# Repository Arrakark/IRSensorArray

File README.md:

# IR Sensor Array

An infra-red sensor array for detecting lines and small objects up to 15cm away.

## PCB Description

### Specs

* 3.3V - 6V input voltage
* Can be used with I2C fast mode using ~2k pullups (try 10k first)
* Can detect lines with high precision and speed
* Can detect objects and surfaces up to 15cm away
* Uses 4-pin JST-XH headers for power and data
* Power and data be daisychained

This project was created using KiCad 5 RC2. Use it to open and edit this design.

### BOM

|      |                                      |                                                               |            |                         |                    |  |  | 
|------|--------------------------------------|---------------------------------------------------------------|------------|-------------------------|--------------------|--|--| 
| "Id" | "Designator"                         | "Package"                                                     | "Quantity" | "Designation"           | "Supplier and ref" |  |  | 
| 1    | "MH2,MH1"                            | "MountingHole_3.2mm_M3"                                       | 2          | "MountingHole_3.2mm_M3" |                    |  |  | 
| 2    | "C1"                                 | "C_Disc_D5.1mm_W3.2mm_P5.00mm"                                | 1          | "0.1uF"                 |                    |  |  | 
| 3    | "C2"                                 | "CP_Radial_D5.0mm_P2.00mm"                                    | 1          | "10uF"                  |                    |  |  | 
| 4    | "C4"                                 | "C_Disc_D5.1mm_W3.2mm_P5.00mm"                                | 1          | "100nF"                 |                    |  |  | 
| 5    | "D1,D2,D3,D4,D5,D6,D7,D8"            | "LED_D5.0mm"                                                  | 8          | "EMITTER"               |                    |  |  | 
| 6    | "J1"                                 | "Measurement_Point_Round-TH_Small"                            | 1          | "EXT_REF"               |                    |  |  | 
| 7    | "Q1,Q2,Q3,Q5,Q6,Q7,Q8,Q4"            | "LED_D5.0mm"                                                  | 8          | "QSD124"                |                    |  |  | 
| 8    | "R1,R2,R4,R6,R8,R10,R12,R14,R16,R18" | "R_Axial_DIN0207_L6.3mm_D2.5mm_P2.54mm_Vertical"              | 10         | "10k0"                  |                    |  |  | 
| 9    | "R3,R5,R7,R9,R11,R13,R15,R17"        | "R_Axial_DIN0207_L6.3mm_D2.5mm_P2.54mm_Vertical"              | 8          | "330R"                  |                    |  |  | 
| 10   | "U1"                                 | "TSSOP-16_4.4x5mm_Pitch0.65mm"                                | 1          | "ADS7828"               |                    |  |  | 
| 11   | "J2"                                 | "JST_XH_B04B-XH-A_04x2.50mm_Straight"                         | 1          | "INPUT"                 |                    |  |  | 
| 12   | "J3"                                 | "JST_XH_B04B-XH-A_04x2.50mm_Straight"                         | 1          | "PASSTHRU"              |                    |  |  | 
| 13   | "JP1"                                | "SolderJumper-3_P1.3mm_Open_RoundedPad1.0x1.5mm_NumberLabels" | 1          | "SB_0"                  |                    |  |  | 
| 14   | "JP2"                                | "SolderJumper-3_P1.3mm_Open_RoundedPad1.0x1.5mm_NumberLabels" | 1          | "REF_5V"                |                    |  |  | 
| 15   | "JP3"                                | "SolderJumper-3_P1.3mm_Open_RoundedPad1.0x1.5mm_NumberLabels" | 1          | "SB_1"                  |                    |  |  | 
| 16   | "G***"                               | "rover"                                                       | 1          | "LOGO"                  |                    |  |  | 

## Installing

Install the sensor array using two M3 screws and standoffs.

## Signal Control

Use the library included with this repo to read the values of the sensors. 

Use the following code to create a sensor array object:
```
SensorArray array1(lookup_table, I2C ID);
```
See the header file for an example.

## License

This project is licensed under the MIT License - see the [LICENSE.md](https://github.com/Arrakark/IRSensorArray/blob/master/LICENSE) file for details

## Acknowledgments

* Special thanks to the V2FC robot team!

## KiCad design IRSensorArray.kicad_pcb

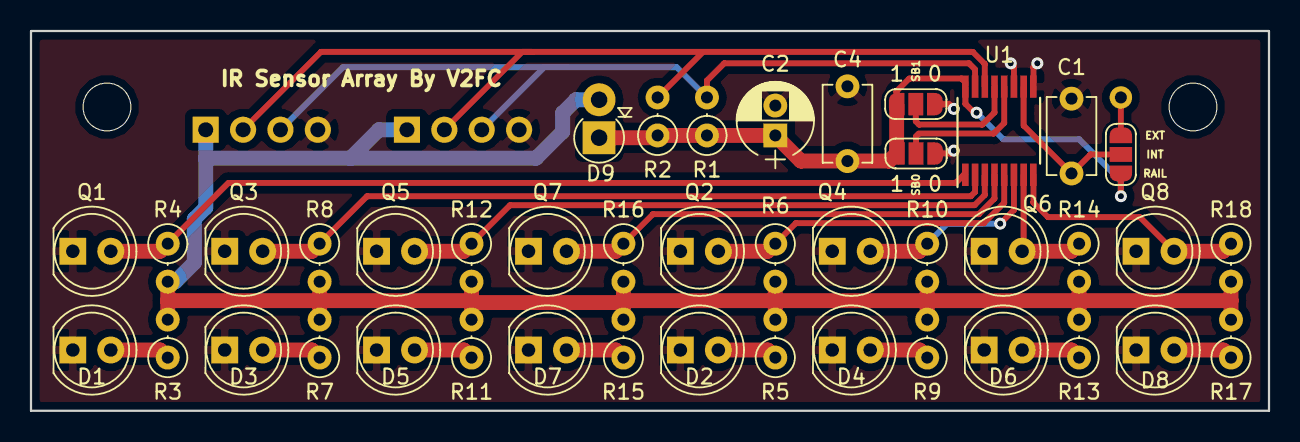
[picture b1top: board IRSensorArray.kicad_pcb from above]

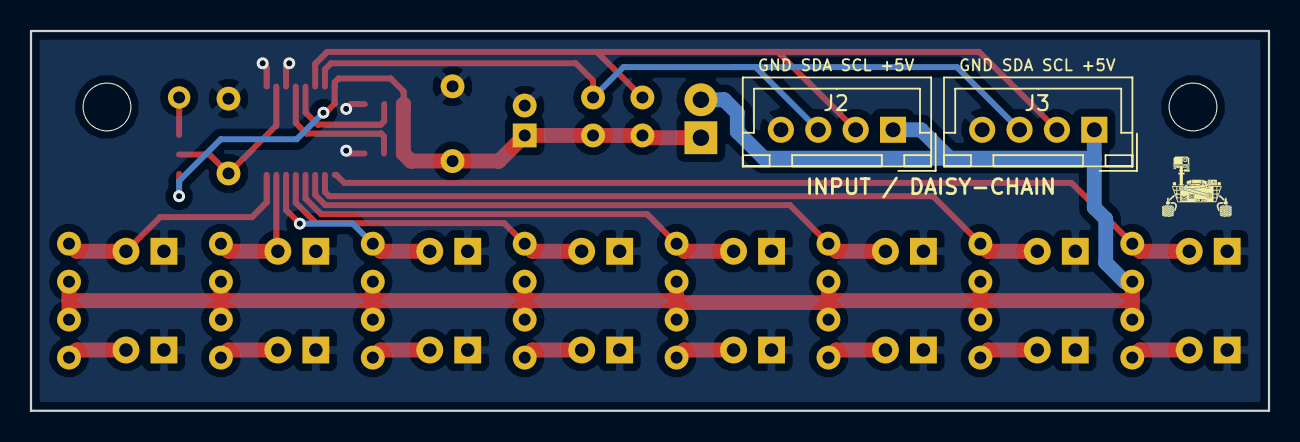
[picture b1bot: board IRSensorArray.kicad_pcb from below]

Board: 2 copper layers, 82.8 x 25.4 mm, 47 parts (2 on the bottom side), 25 nets.

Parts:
C1: 0.1uF; C_Disc_D5.1mm_W3.2mm_P5.00mm
C2: 10uF; CP_Radial_D5.0mm_P2.00mm
C4: 100nF; C_Disc_D5.1mm_W3.2mm_P5.00mm
D1, D2, D3, D4, D5, D6, D7, D8: HSDL-4420; LED_D5.0mm
D9: 1N4007; D_DO-41_SOD81_P2.54mm_Vertical_AnodeUp
J1: EXT_REF; Measurement_Point_Round-TH_Small
J2: INPUT; JST_XH_B04B-XH-A_04x2.50mm_Straight
J3: PASSTHRU; JST_XH_B04B-XH-A_04x2.50mm_Straight
JP1: SB_0; SolderJumper-3_P1.3mm_Open_RoundedPad1.0x1.5mm_NumberLabels
JP2: REF_5V; SolderJumper-3_P1.3mm_Open_RoundedPad1.0x1.5mm_NumberLabels
JP3: SB_1; SolderJumper-3_P1.3mm_Open_RoundedPad1.0x1.5mm_NumberLabels
MH1, MH2: MountingHole_3.2mm_M3
Q1, Q2, Q3, Q4, Q5, Q6, Q7, Q8: QSD124; LED_D5.0mm
R1, R2, R4, R6, R8, R10, R12, R14, R16, R18: 10k0; R_Axial_DIN0207_L6.3mm_D2.5mm_P2.54mm_Vertical
R3, R5, R7, R9, R11, R13, R15, R17: 330R; R_Axial_DIN0207_L6.3mm_D2.5mm_P2.54mm_Vertical
U1: ADS7828; TSSOP-16_4.4x5mm_Pitch0.65mm

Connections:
+5V: C2.1, C4.1, D9.1, JP1.1, JP2.1, JP3.1, R1.1, R2.1, U1.16
/CH0: Q1.2, R4.1, U1.1
/CH1: Q3.2, R8.1, U1.2
/CH2: Q5.2, R12.1, U1.3
/CH3: Q7.2, R16.1, U1.4
/CH4: Q2.2, R6.1, U1.5
/CH5: Q4.2, R10.1, U1.6
/CH6: Q6.2, R14.1, U1.7
/CH7: Q8.2, R18.1, U1.8
/REF: C1.1, JP2.2, U1.10
/SB_0: JP1.2, U1.12
/SB_1: JP3.2, U1.13
/SCL: J2.2, J3.2, R2.2, U1.14
/SDA: J2.3, J3.3, R1.2, U1.15
GND: C1.2, C2.2, C4.2, D1.1, D2.1, D3.1, D4.1, D5.1, D6.1, D7.1, D8.1, J2.4, J3.4, JP1.3, JP3.3, Q1.1, Q2.1, Q3.1, Q4.1, Q5.1, Q6.1, Q7.1, Q8.1, U1.9, U1.11
unnamed: D1.2, R3.1
unnamed: D2.2, R5.1
unnamed: D3.2, R7.1
unnamed: D4.2, R9.1
unnamed: D5.2, R11.1
unnamed: D6.2, R13.1
unnamed: D7.2, R15.1
unnamed: D8.2, R17.1
unnamed: J1.1, JP2.3
VCC: D9.2, J2.1, J3.1, R3.2, R4.2, R5.2, R6.2, R7.2, R8.2, R9.2, R10.2, R11.2, R12.2, R13.2, R14.2, R15.2, R16.2, R17.2, R18.2

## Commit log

2018-06-14 Started schematic, leaving rest
2018-06-19 Connected jumpers and ADC
2018-06-19 Added sensor array
2018-06-19 Started PCB
2018-06-19 Changed triangle solder bridges to semi-circle
2018-06-19 Added mounting holes and some fixes
2018-06-19 Started PCB layout
2018-06-20 First draft finished!
2018-06-20 Added images
2018-06-20 Added png images
2018-06-20 Added library for sensor
2018-06-20 Added reverse voltage diode
2018-06-20 Added new gerber files
2018-06-20 Final edit
